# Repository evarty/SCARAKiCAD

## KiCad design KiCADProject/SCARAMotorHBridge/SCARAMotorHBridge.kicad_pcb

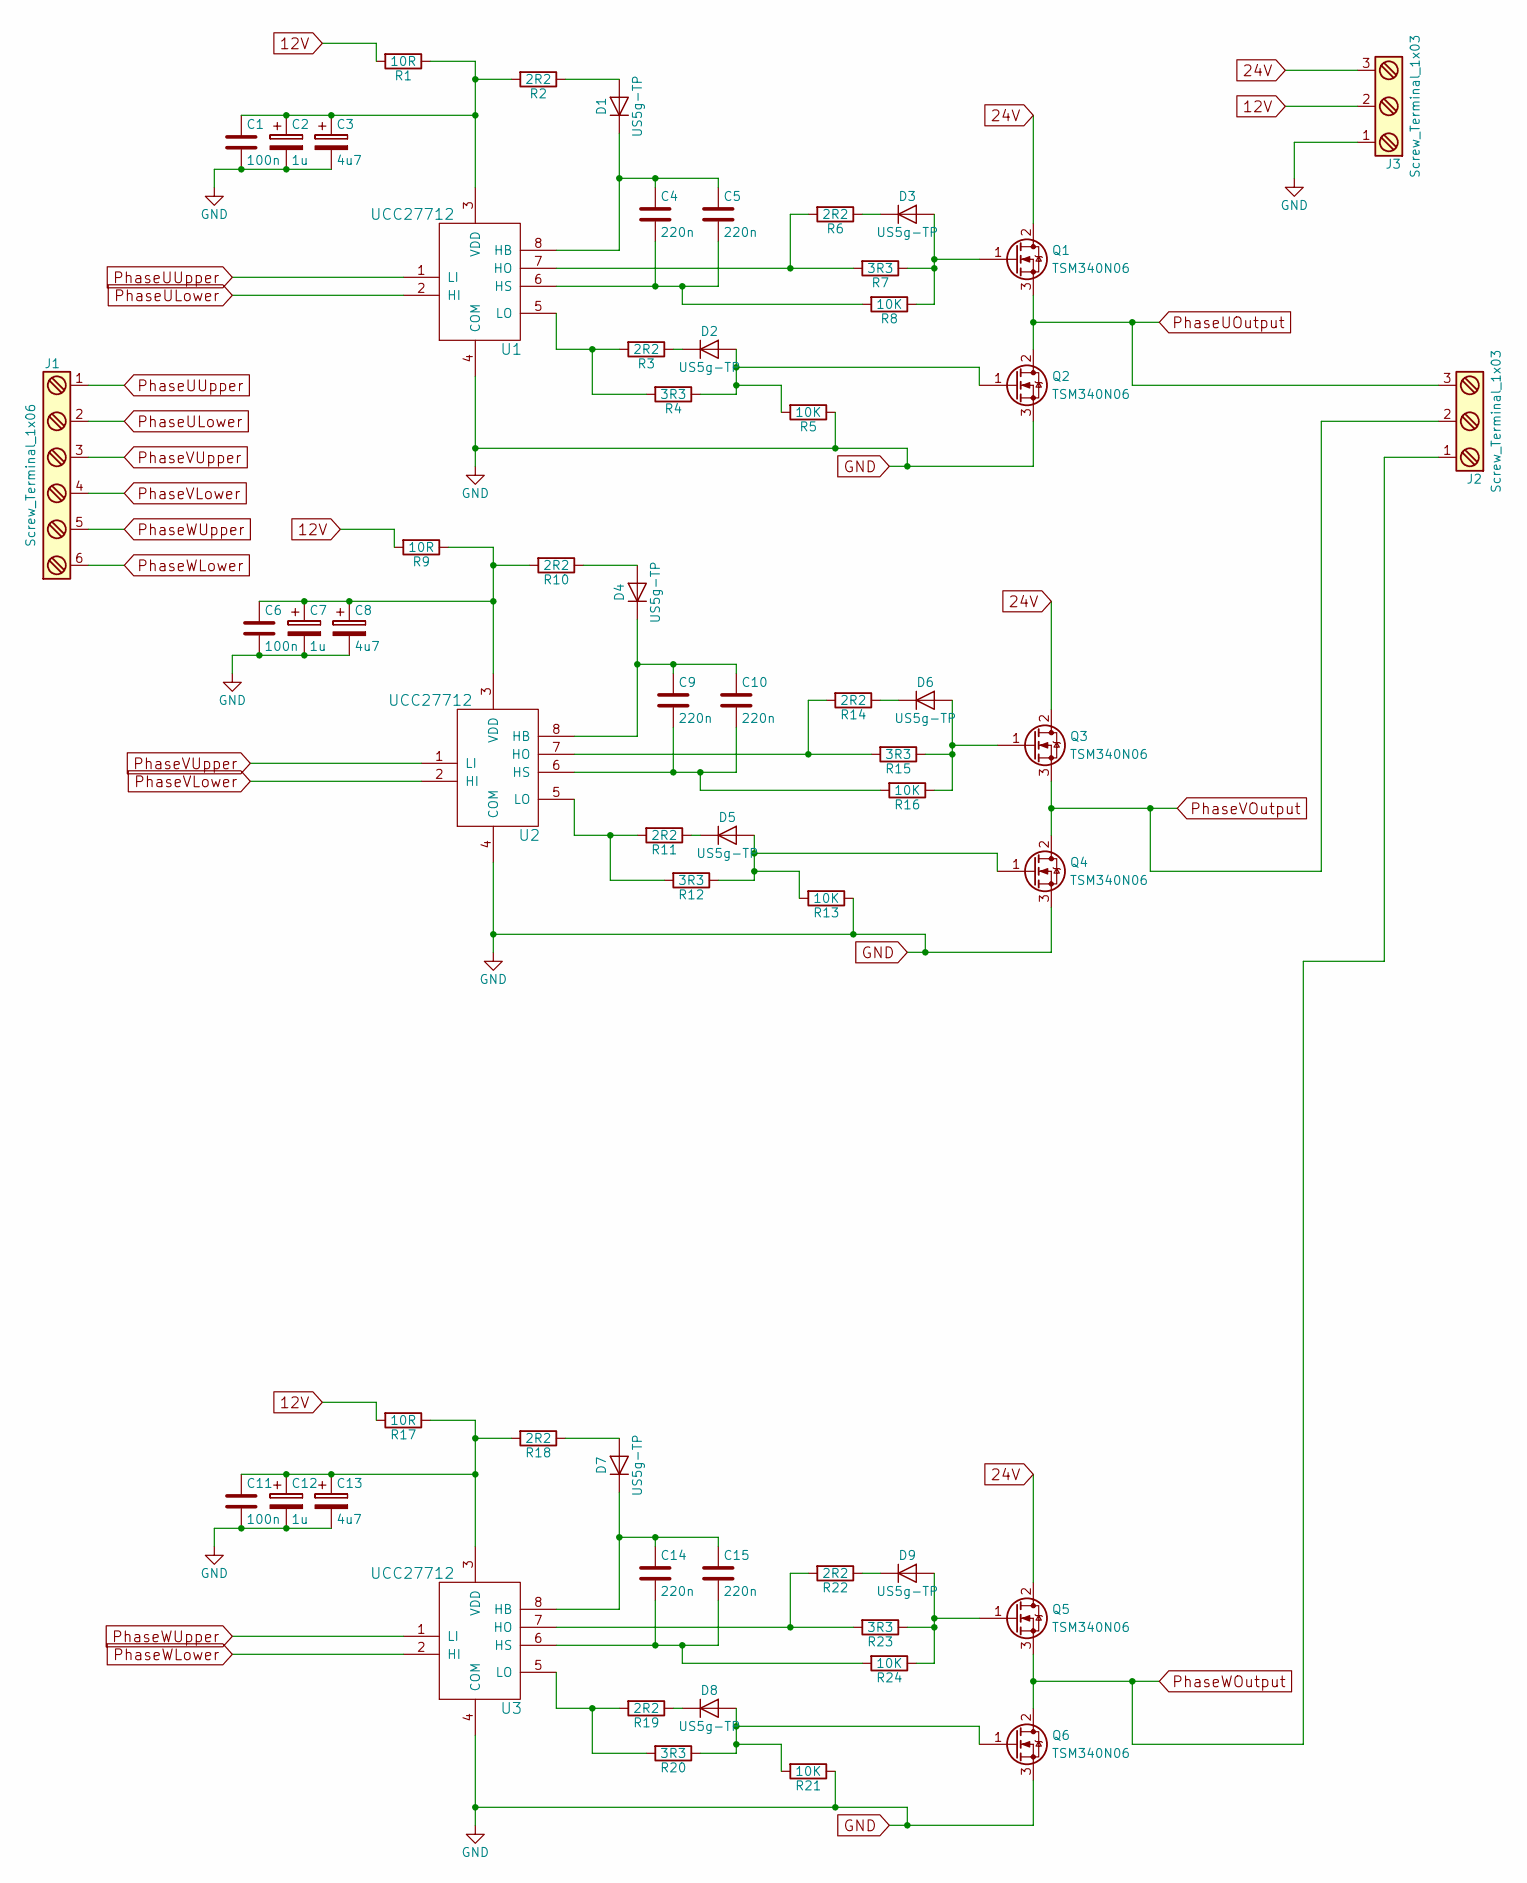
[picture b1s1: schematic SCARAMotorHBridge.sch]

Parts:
C1, C6, C11: 100n; C_0603_HandSoldering
C2, C7, C12: 1u; C_0805_HandSoldering
C3, C8, C13: 4u7; C_0805_HandSoldering
C4, C5, C9, C10, C14, C15: 220n; C_0805_HandSoldering
D1, D2, D3, D4, D5, D6, D7, D8, D9: US5g-TP; DO-214AB_Handsoldering
J1: Screw_Terminal_1x06; 6TermScrewTerminal
J2, J3: Screw_Terminal_1x03; 3TermScrewTerminal
Q1, Q2, Q3, Q4, Q5, Q6: TSM340N06; TO-252-2Lead
R1, R9, R17: 10R; R_1206_HandSoldering
R2, R3, R6, R10, R11, R14, R18, R19, R22: 2R2; R_1206_HandSoldering
R4, R7, R12, R15, R20, R23: 3R3; R_1206_HandSoldering
R5, R8, R13, R16, R21, R24: 10K; R_0805_HandSoldering
U1, U2, U3: UCC27712; SOIC-8-N

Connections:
12V: J3.2, R1.2, R9.2, R17.2
24V: J3.3, Q1.2 (D), Q3.2 (D), Q5.2 (D)
GND: C1.2, C2.2, C3.2, C6.2, C7.2, C8.2, C11.2, C12.2, C13.2, J3.1, Q2.3 (S), Q4.3 (S), Q6.3 (S), R5.1, R13.1, R21.1, U1.4 (COM), U2.4 (COM), U3.4 (COM)
unnamed: C1.1, C2.1, C3.1, R1.1, R2.2, U1.3 (VDD)
unnamed: C4.1, C5.1, D1.1 (K), U1.8 (HB)
unnamed: C4.2, C5.2, R8.2, U1.6 (HS)
unnamed: C6.1, C7.1, C8.1, R9.1, R10.2, U2.3 (VDD)
unnamed: C9.1, C10.1, D4.1 (K), U2.8 (HB)
unnamed: C9.2, C10.2, R16.2, U2.6 (HS)
unnamed: C11.1, C12.1, C13.1, R17.1, R18.2, U3.3 (VDD)
unnamed: C14.1, C15.1, D7.1 (K), U3.8 (HB)
unnamed: C14.2, C15.2, R24.2, U3.6 (HS)
unnamed: D1.2 (A), R2.1
unnamed: D2.1 (K), R3.1
unnamed: D2.2 (A), Q2.1 (G), R4.1, R5.2
unnamed: D3.1 (K), R6.1
unnamed: D3.2 (A), Q1.1 (G), R7.1, R8.1
unnamed: D4.2 (A), R10.1
unnamed: D5.1 (K), R11.1
unnamed: D5.2 (A), Q4.1 (G), R12.1, R13.2
unnamed: D6.1 (K), R14.1
unnamed: D6.2 (A), Q3.1 (G), R15.1, R16.1
unnamed: D7.2 (A), R18.1
unnamed: D8.1 (K), R19.1
unnamed: D8.2 (A), Q6.1 (G), R20.1, R21.2
unnamed: D9.1 (K), R22.1
unnamed: D9.2 (A), Q5.1 (G), R23.1, R24.1
unnamed: R3.2, R4.2, U1.5 (LO)
unnamed: R6.2, R7.2, U1.7 (HO)
unnamed: R11.2, R12.2, U2.5 (LO)
unnamed: R14.2, R15.2, U2.7 (HO)
unnamed: R19.2, R20.2, U3.5 (LO)
unnamed: R22.2, R23.2, U3.7 (HO)
PhaseULower: J1.2, U1.2 (HI)
PhaseUOutput: J2.3, Q1.3 (S), Q2.2 (D)
PhaseUUpper: J1.1, U1.1 (LI)
PhaseVLower: J1.4, U2.2 (HI)
PhaseVOutput: J2.2, Q3.3 (S), Q4.2 (D)
PhaseVUpper: J1.3, U2.1 (LI)
PhaseWLower: J1.6, U3.2 (HI)
PhaseWOutput: J2.1, Q5.3 (S), Q6.2 (D)
PhaseWUpper: J1.5, U3.1 (LI)

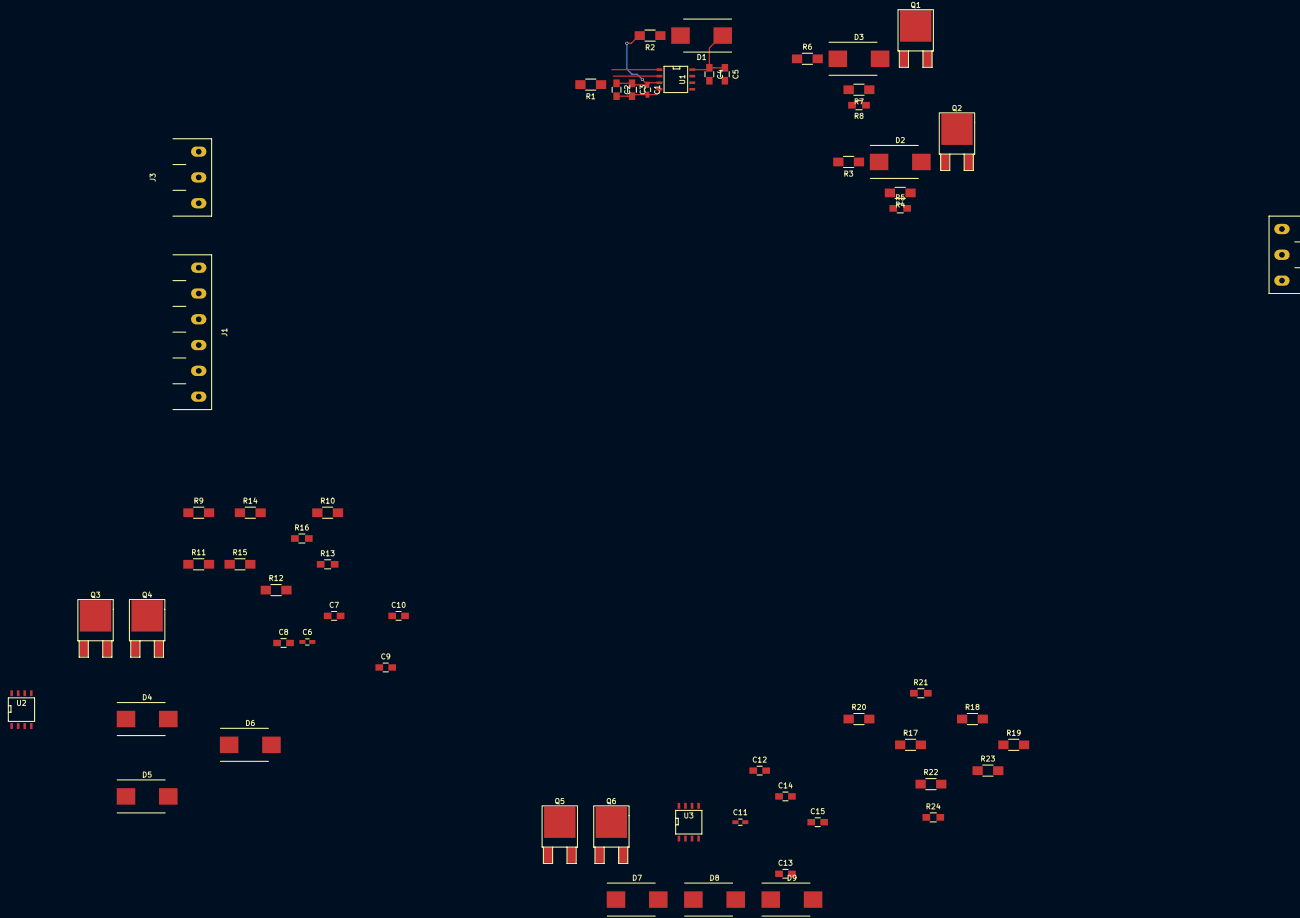
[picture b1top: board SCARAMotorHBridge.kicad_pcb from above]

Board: 2 copper layers, 60 parts (0 on the bottom side), 42 nets.

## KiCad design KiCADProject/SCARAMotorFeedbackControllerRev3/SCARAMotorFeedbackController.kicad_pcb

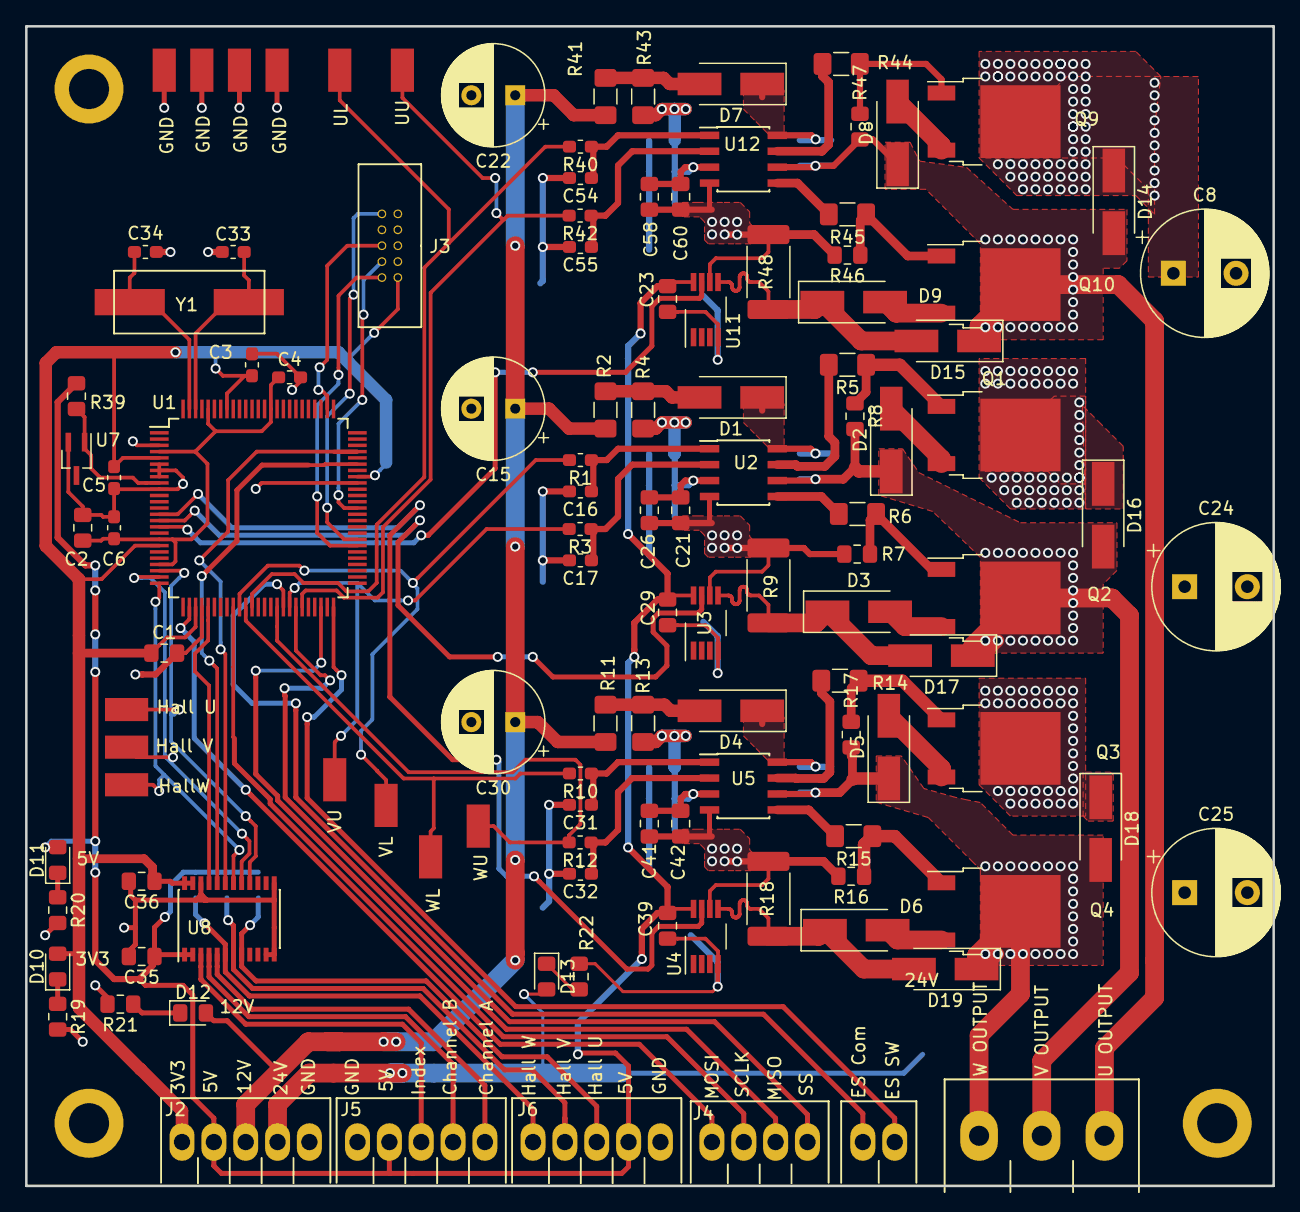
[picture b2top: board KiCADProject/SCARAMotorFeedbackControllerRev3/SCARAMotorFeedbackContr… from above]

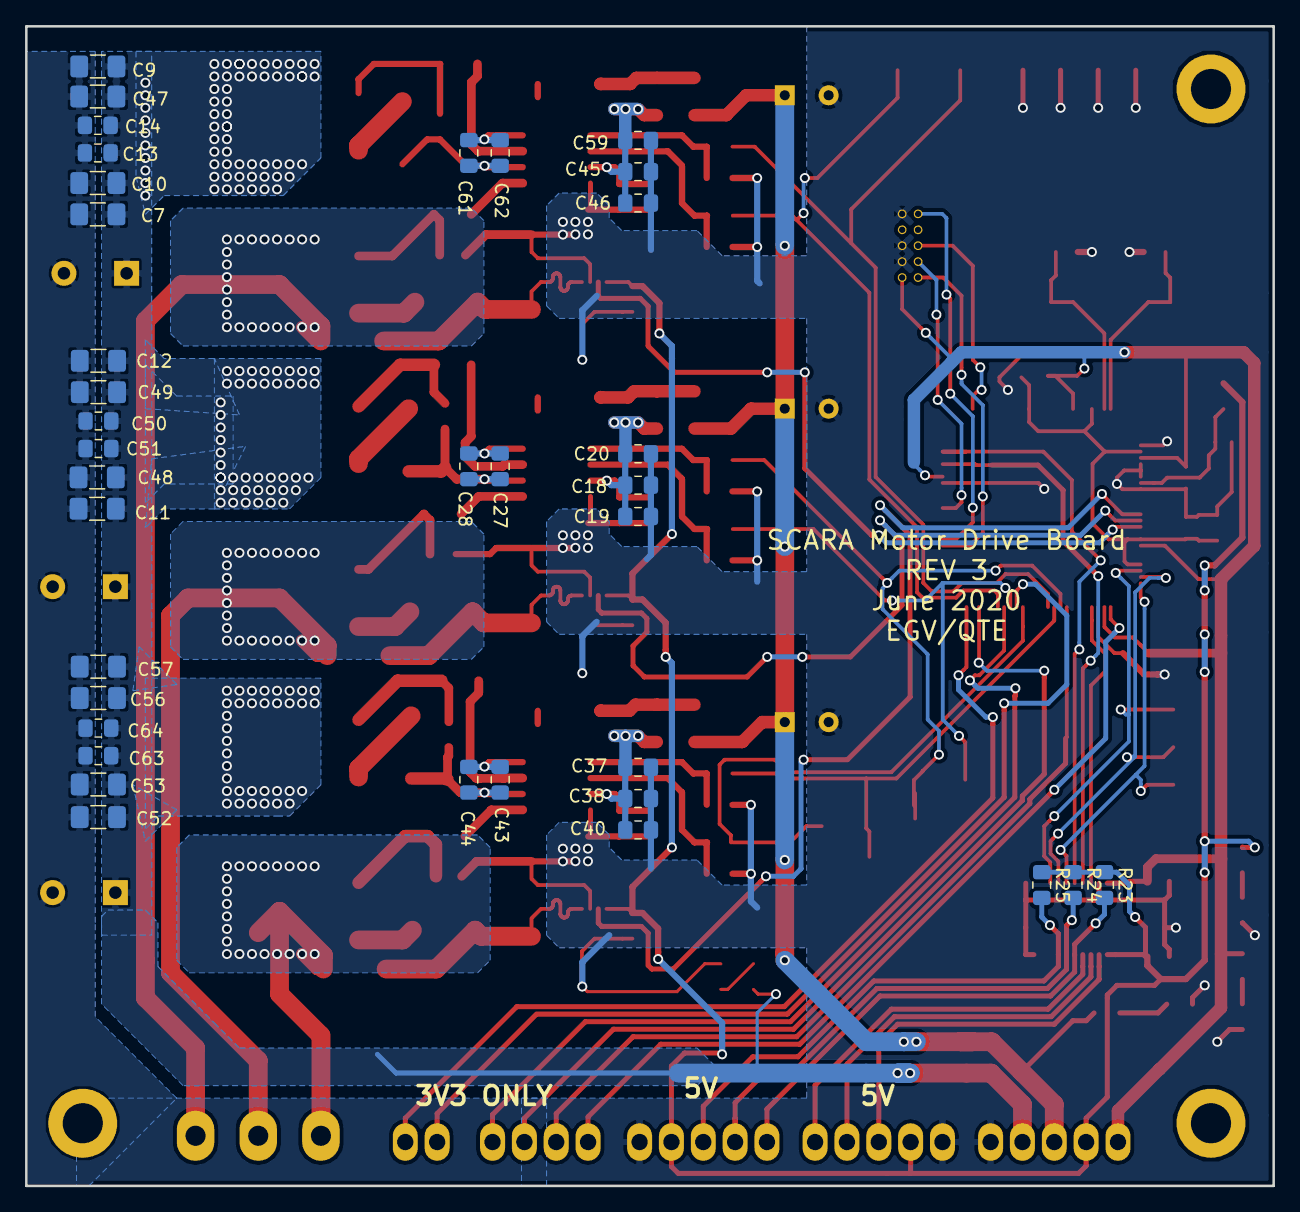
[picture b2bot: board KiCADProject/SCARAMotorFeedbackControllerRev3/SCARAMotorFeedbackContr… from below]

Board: 2 copper layers, 99.5 x 92.5 mm, 154 parts (36 on the bottom side), 83 nets.

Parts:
C1, C2: 1u; C_0805_2012Metric_Pad1.15x1.40mm_HandSolder
C3, C4: 0u1; C_0603_1608Metric_Pad1.05x0.95mm_HandSolder
C5, C6: 10n; C_0603_1608Metric_Pad1.05x0.95mm_HandSolder
C7, C9, C10, C11, C12, C47, C48, C49, C52, C53, C56, C57: 10u; C_1206_3216Metric_Pad1.42x1.75mm_HandSolder
C8, C24, C25: 470u; CP_Radial_D10.0mm_P5.00mm
C13, C14, C50, C51, C63, C64: u1; C_0805_2012Metric_Pad1.15x1.40mm_HandSolder
C15, C22, C30: 47u; CP_Radial_D8.0mm_P3.50mm
C16, C17, C31, C32, C54, C55: 120p; C_0603_1608Metric_Pad1.05x0.95mm_HandSolder
C18, C19, C37, C38, C45, C46: 10u; C_0805_2012Metric_Pad1.15x1.40mm_HandSolder
C20, C21, C26, C27, C28, C40, C41, C42, C43, C44, C58, C59, C60, C61, C62: u22; C_0805_2012Metric_Pad1.15x1.40mm_HandSolder
C23, C29, C35, C36, C39: 0u1; C_0805_2012Metric_Pad1.15x1.40mm_HandSolder
C33, C34: 13p; C_0603_1608Metric_Pad1.05x0.95mm_HandSolder
D1, D2, D3, D4, D5, D6, D7, D8, D9, D14, D15, D16, D17, D18, D19: D; D_SMA_Handsoldering
D10, D11, D12, D13: LED_ALT; LED_0805_2012Metric_Pad1.15x1.40mm_HandSolder
GND: TestPoint
GND#2, GND#3, GND#4: TestPoint
Hall U: TestPoint
Hall V: TestPoint
HallW: TestPoint
J1: Conn_01x02_Female; 2TermScrewTerminal
J2: Screw_Terminal_01x05; 5TermScrewTerminal
J3: SWD/JTAG Header; SWDHeader
J4: SPI Header; 4TermScrewTerminal
J5: EncoderInput; 5TermScrewTerminal
J6: HallInput; 5TermScrewTerminal
J9: Screw_Terminal_1x03; 3TermScrewTerminal
Q1, Q2, Q3, Q4, Q9, Q10: Q_NMOS_GDS; TO-252-2
R1, R3, R10, R12, R40, R42: 59R; R_0603_1608Metric_Pad1.05x0.95mm_HandSolder
R2, R4, R11, R13, R41, R43: 2R2; R_1206_3216Metric_Pad1.42x1.75mm_HandSolder
R5, R6, R14, R15, R44, R45: 3R3; R_1206_3216Metric_Pad1.42x1.75mm_HandSolder
R7, R8, R16, R17, R46, R47: 10K; R_0805_2012Metric_Pad1.15x1.40mm_HandSolder
R9, R18, R48: R05; R_2512_6332Metric_Pad1.52x3.35mm_HandSolder
R19, R39: 120R; R_0805_2012Metric_Pad1.15x1.40mm_HandSolder
R20: 240R; R_0805_2012Metric_Pad1.15x1.40mm_HandSolder
R21, R22: 1K; R_0805_2012Metric_Pad1.15x1.40mm_HandSolder
R23, R24, R25: 2k2; R_0805_2012Metric_Pad1.15x1.40mm_HandSolder
U1: ATSAM4E16CB-AN-ND; LQFP-100_14x14mm_P0.5mm
U2, U5, U12: UCC27712; SOIC-8_3.9x4.9mm_P1.27mm
U3, U4, U11: INA2180; VSSOP-8_3.0x3.0mm_P0.65mm
U7: LM4040; SOT-323_SC-70_Handsoldering
U8: 74LVC4245A; TSSOP-24_4.4x7.8mm_P0.65mm
UL: TestPoint
UU: TestPoint
VL: TestPoint
VU: TestPoint
WL: TestPoint
WU: TestPoint
Y1: 12MHzCrystal; SMDCrystalABLS12

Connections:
3V3: C1.1, C3.1, C5.1, C36.1, D10.2, J2.5, J3.1, U1.5, U1.19, U1.28, U1.68, U1.93, U8.23, U8.24
3V3Ref: R39.2, U1.9, U7.1
5V: C23.1, C29.1, C35.1, C39.1, D11.2, J2.4, J5.4, J6.2, R23.1, R24.1, R25.1, R39.1, U3.8, U4.8, U8.1, U8.2, U11.8
12V: C15.1, C22.1, C30.1, D12.2, J2.3, R2.2, R11.2, R41.2
24V: C7.1, C8.1, C9.1, C10.1, C11.1, C12.1, C13.1, C14.1, C24.1, C25.1, C47.1, C48.1, C49.1, C50.1, C51.1, C52.1, C53.1, C56.1, C57.1, C63.1, C64.1, D13.2, D14.1, D16.1, D18.1, J2.2, Q1.2, Q3.2, Q9.2
ChannelA: J5.1, U8.5
ChannelAShift: U1.72, U8.19
ChannelB: J5.2, U8.4
ChannelBShift: U1.70, U8.20
CurrentSenseU: U1.16, U11.7
CurrentSenseV: U1.15, U3.7
CurrentSenseW: U1.14, U4.7
EndstopCommon: J1.2, U1.42
EndstopSwitch: J1.1, U1.50
GND: C1.2, C2.2, C3.2, C4.2, C5.2, C6.2, C7.2, C8.2, C9.2, C10.2, C11.2, C12.2, C13.2, C14.2, C15.2, C16.2, C17.2, C18.2, C19.2, C20.2, C21.2, C22.2, C23.2, C24.2, C25.2, C26.2, C29.2, C30.2, C31.2, C32.2, C33.1, C34.1, C35.2, C36.2, C37.2, C38.2, C39.2, C40.2, C41.2, C42.2, C45.2, C46.2, C47.2, C48.2, C49.2, C50.2, C51.2, C52.2, C53.2, C54.2, C55.2, C56.2, C57.2, C58.2, C59.2, C60.2, C63.2, C64.2, GND.1, GND#2.1, GND#3.1, GND#4.1, J2.1, J3.3, J3.5, J3.9, J5.5, J6.1, R7.2, R9.2, R16.2, R18.2, R19.2, R20.2, R21.2, R22.2, R46.2, R48.2, U1.3, U1.6, U1.7, U1.8, U1.10, U1.29, U1.67, U2.4, U3.4, U3.6, U4.4, U4.6, U5.4, U7.2, U8.11, U8.12, U8.13, U8.22, U11.4, U11.6, U12.4
HallU: J6.3, R25.2, U8.8
HallUShift: Hall U.1, U1.23, U8.16
HallV: J6.4, R24.2, U8.7
HallVShift: Hall V.1, U1.24, U8.17
HallW: J6.5, R23.2, U8.6
HallWShift: HallW.1, U1.25, U8.18
IN+2U: D9.1, D15.2, R48.1, U11.5
IN+2V: D3.1, D17.2, R9.1, U3.5
IN+2W: D6.1, D19.2, R18.1, U4.5
Index: J5.3, U8.3
IndexShift: U1.30, U8.21
MISO: J4.2, U1.48
MOSI: J4.4, U1.27
unnamed: C2.1, C4.1, C6.1, U1.4, U1.18, U1.22, U1.86, U1.96
unnamed: C16.1, R1.1, U2.1
unnamed: C17.1, R3.1, U2.2
unnamed: C18.1, C19.1, C20.1, C21.1, C26.1, R4.1, U2.3
unnamed: C27.2, C28.2, D1.1, U2.8
unnamed: C31.1, R10.1, U5.1
unnamed: C32.1, R12.1, U5.2
unnamed: C33.2, U1.98, Y1.1
unnamed: C34.2, U1.99, Y1.2
unnamed: C37.1, C38.1, C40.1, C41.1, C42.1, R13.1, U5.3
unnamed: C43.2, C44.2, D4.1, U5.8
unnamed: C45.1, C46.1, C58.1, C59.1, C60.1, R43.1, U12.3
unnamed: C54.1, R40.1, U12.1
unnamed: C55.1, R42.1, U12.2
unnamed: C61.2, C62.2, D7.1, U12.8
unnamed: D1.2, R2.1, R4.2
unnamed: D2.2, Q1.3
unnamed: D3.2, Q2.3
unnamed: D4.2, R11.1, R13.2
unnamed: D5.2, Q3.3
unnamed: D6.2, Q4.3
unnamed: D7.2, R41.1, R43.2
unnamed: D8.2, Q9.3
unnamed: D9.2, Q10.3
unnamed: D10.1, R19.1
unnamed: D11.1, R20.1
unnamed: D12.1, R21.1
unnamed: D13.1, R22.1
unnamed: Q1.1, R5.1, R8.1
unnamed: Q2.1, R6.1, R7.1
unnamed: Q3.1, R14.1, R17.1
unnamed: Q4.1, R15.1, R16.1
unnamed: Q9.1, R44.1, R47.1
unnamed: Q10.1, R45.1, R46.1
unnamed: R5.2, U2.7
unnamed: R6.2, U2.5
unnamed: R14.2, U5.7
unnamed: R15.2, U5.5
unnamed: R44.2, U12.7
unnamed: R45.2, U12.5
PhaseULower: R40.2, U1.37, UL.1
PhaseUOutput: C61.1, C62.1, D8.1, D14.2, D15.1, J9.3, Q10.2, R47.2, U12.6
PhaseUUpper: R42.2, U1.45, UU.1
PhaseVLower: R1.2, U1.35, VL.1
PhaseVOutput: C27.1, C28.1, D2.1, D16.2, D17.1, J9.2, Q2.2, R8.2, U2.6
PhaseVUpper: R3.2, U1.43, VU.1
PhaseWLower: R10.2, U1.36, WL.1
PhaseWOutput: C43.1, C44.1, D5.1, D18.2, D19.1, J9.1, Q4.2, R17.2, U5.6
PhaseWUpper: R12.2, U1.41, WU.1
SCLK: J4.3, U1.34
SS: J4.1, U1.44
SWDCLK: J3.4, U1.63
SWDIO: J3.2, U1.57
SWO: J3.6, U1.77
nRESET: J3.10, U1.58

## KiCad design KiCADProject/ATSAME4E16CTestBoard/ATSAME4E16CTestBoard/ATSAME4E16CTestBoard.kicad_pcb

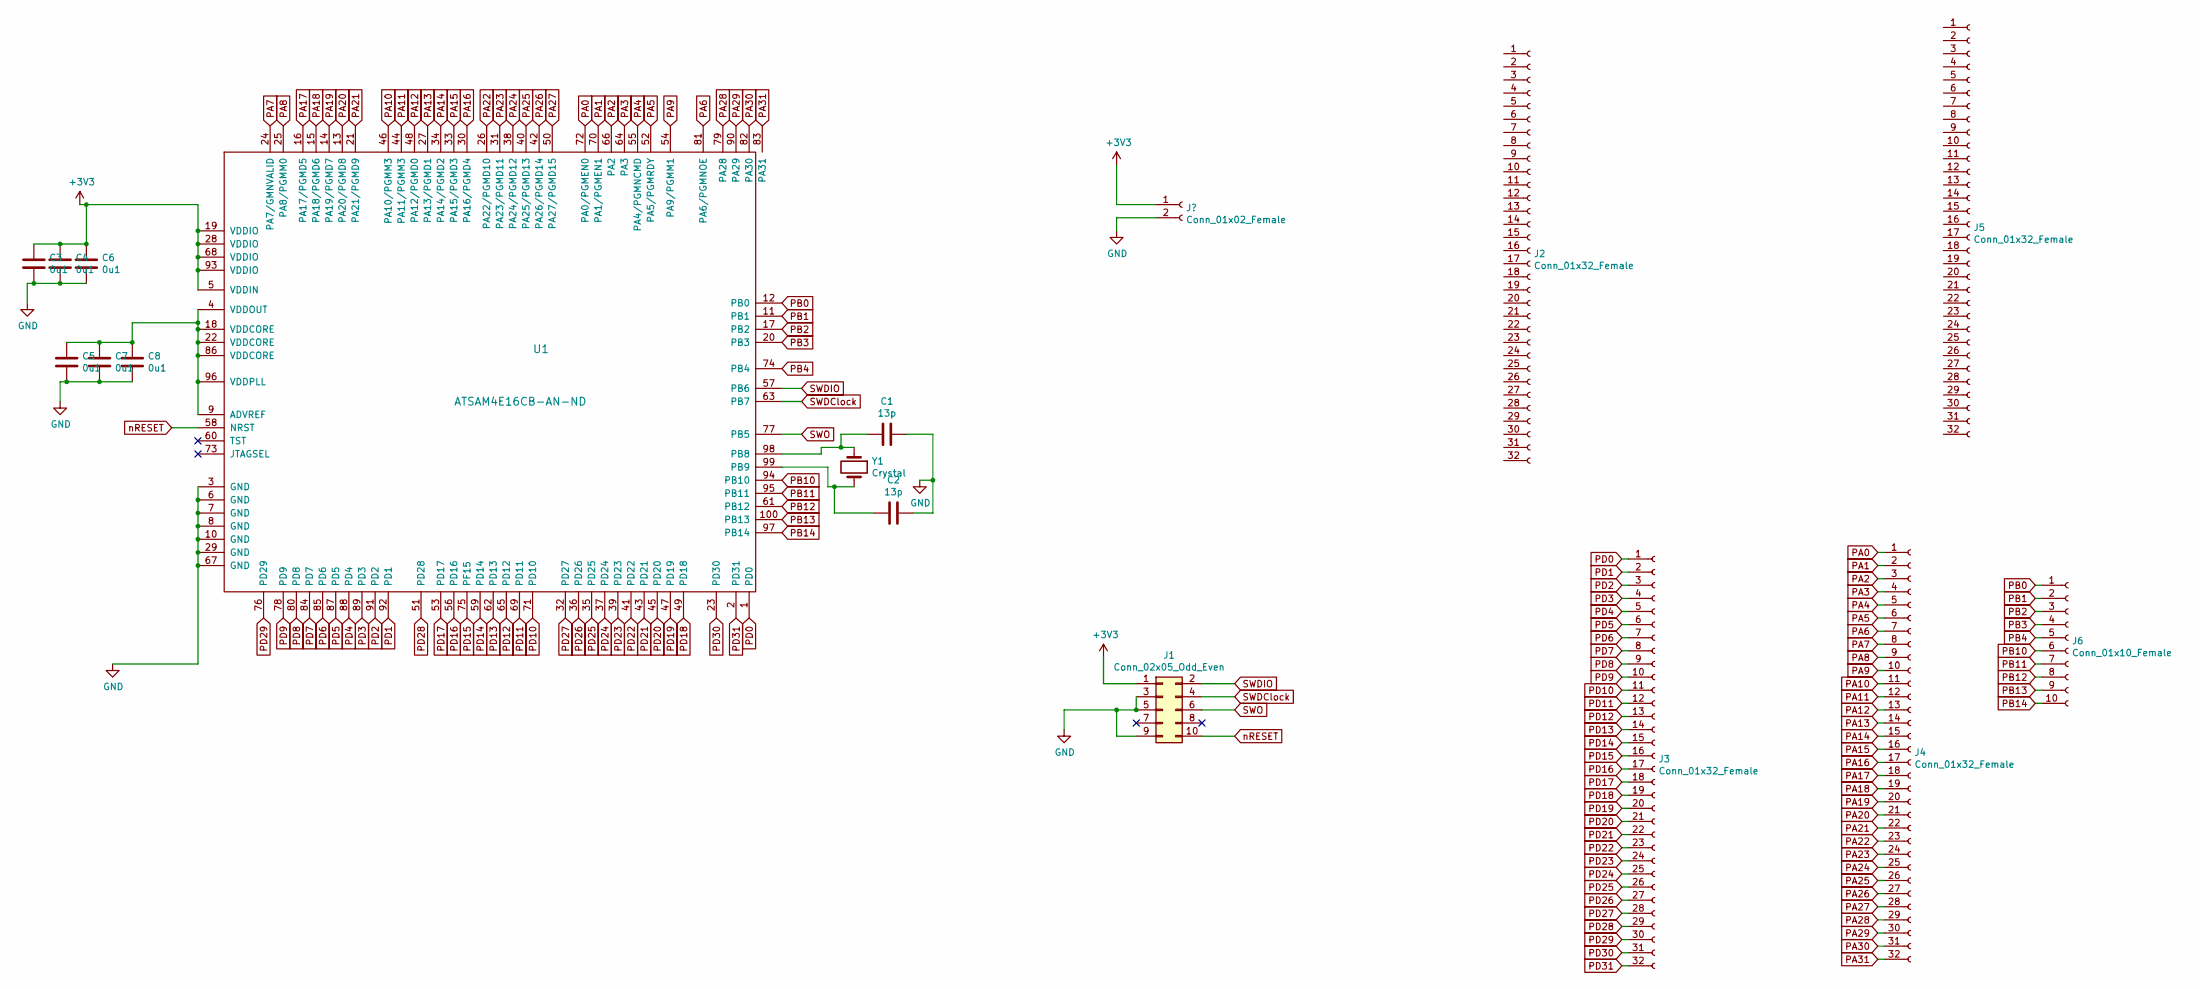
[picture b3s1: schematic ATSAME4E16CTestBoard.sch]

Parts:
C1, C2: 13p; C_0603_1608Metric_Pad1.05x0.95mm_HandSolder
C3, C4, C5, C6, C7, C8: 0u1; C_0603_1608Metric_Pad1.05x0.95mm_HandSolder
J1: Conn_02x05_Odd_Even; SWDHeader
J2, J3, J4, J5: Conn_01x32_Female; PinHeader_1x32_P2.54mm_Vertical
J6: Conn_01x10_Female; PinHeader_1x10_P2.54mm_Vertical
U1: ATSAM4E16CB-AN-ND; TQFP-100_12x12mm_P0.4mm
Y1: Crystal; SMDCrystalABLS12

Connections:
+3V3: C3.1, C4.1, C6.1, J1.1, U1.5 (VDDIN), U1.19 (VDDIO), U1.28 (VDDIO), U1.68 (VDDIO), U1.93 (VDDIO)
GND: C1.1, C2.1, C3.2, C4.2, C5.2, C6.2, C7.2, C8.2, J1.3, J1.5, J1.9, U1.3 (GND), U1.6 (GND), U1.7 (GND), U1.8 (GND), U1.10 (GND), U1.29 (GND), U1.67 (GND)
unnamed: C1.2, U1.98 (PB8), Y1.1
unnamed: C2.2, U1.99 (PB9), Y1.2
unnamed: C5.1, C7.1, C8.1, U1.4 (VDDOUT), U1.9 (ADVREF), U1.18 (VDDCORE), U1.22 (VDDCORE), U1.86 (VDDCORE), U1.96 (VDDPLL)
PA0: J4.1, U1.72 (PA0/PGMEN0)
PA1: J4.2, U1.70 (PA1/PGMEN1)
PA2: J4.3, U1.66 (PA2)
PA3: J4.4, U1.64 (PA3)
PA4: J4.5, U1.55 (PA4/PGMNCMD)
PA5: J4.6, U1.52 (PA5/PGMRDY)
PA6: J4.7, U1.81 (PA6/PGMNOE)
PA7: J4.8, U1.24 (PA7/GMNVALID)
PA8: J4.9, U1.25 (PA8/PGMM0)
PA9: J4.10, U1.54 (PA9/PGMM1)
PA10: J4.11, U1.46 (PA10/PGMM3)
PA11: J4.12, U1.44 (PA11/PGMM3)
PA12: J4.13, U1.48 (PA12/PGMD0)
PA13: J4.14, U1.27 (PA13/PGMD1)
PA14: J4.15, U1.34 (PA14/PGMD2)
PA15: J4.16, U1.33 (PA15/PGMD3)
PA16: J4.17, U1.30 (PA16/PGMD4)
PA17: J4.18, U1.16 (PA17/PGMD5)
PA18: J4.19, U1.15 (PA18/PGMD6)
PA19: J4.20, U1.14 (PA19/PGMD7)
PA20: J4.21, U1.13 (PA20/PGMD8)
PA21: J4.22, U1.21 (PA21/PGMD9)
PA22: J4.23, U1.26 (PA22/PGMD10)
PA23: J4.24, U1.31 (PA23/PGMD11)
PA24: J4.25, U1.38 (PA24/PGMD12)
PA25: J4.26, U1.40 (PA25/PGMD13)
PA26: J4.27, U1.42 (PA26/PGMD14)
PA27: J4.28, U1.50 (PA27/PGMD15)
PA28: J4.29, U1.79 (PA28)
PA29: J4.30, U1.90 (PA29)
PA30: J4.31, U1.82 (PA30)
PA31: J4.32, U1.83 (PA31)
PB0: J6.1, U1.12 (PB0)
PB1: J6.2, U1.11 (PB1)
PB2: J6.3, U1.17 (PB2)
PB3: J6.4, U1.20 (PB3)
PB4: J6.5, U1.74 (PB4)
PB10: J6.6, U1.94 (PB10)
PB11: J6.7, U1.95 (PB11)
PB12: J6.8, U1.61 (PB12)
PB13: J6.9, U1.100 (PB13)
PB14: J6.10, U1.97 (PB14)
PD0: J3.1, U1.1 (PD0)
PD1: J3.2, U1.92 (PD1)
PD2: J3.3, U1.91 (PD2)
PD3: J3.4, U1.89 (PD3)
PD4: J3.5, U1.88 (PD4)
PD5: J3.6, U1.87 (PD5)
PD6: J3.7, U1.85 (PD6)
PD7: J3.8, U1.84 (PD7)
PD8: J3.9, U1.80 (PD8)
PD9: J3.10, U1.78 (PD9)
PD10: J3.11, U1.71 (PD10)
PD11: J3.12, U1.69 (PD11)
PD12: J3.13, U1.65 (PD12)
PD13: J3.14, U1.62 (PD13)
PD14: J3.15, U1.59 (PD14)
PD15: J3.16, U1.75 (PF15)
PD16: J3.17, U1.56 (PD16)
PD17: J3.18, U1.53 (PD17)
PD18: J3.19, U1.49 (PD18)
PD19: J3.20, U1.47 (PD19)
PD20: J3.21, U1.45 (PD20)
PD21: J3.22, U1.43 (PD21)
PD22: J3.23, U1.41 (PD22)
PD23: J3.24, U1.39 (PD23)
PD24: J3.25, U1.37 (PD24)
PD25: J3.26, U1.35 (PD25)
PD26: J3.27, U1.36 (PD26)
PD27: J3.28, U1.32 (PD27)
PD28: J3.29, U1.51 (PD28)
PD29: J3.30, U1.76 (PD29)
PD30: J3.31, U1.23 (PD30)
PD31: J3.32, U1.2 (PD31)
SWDClock: J1.4, U1.63 (PB7)
SWDIO: J1.2, U1.57 (PB6)
SWO: J1.6, U1.77 (PB5)
nRESET: J1.10, U1.58 (NRST)

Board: 2 copper layers, 16 parts (0 on the bottom side), 83 nets, no tracks yet.

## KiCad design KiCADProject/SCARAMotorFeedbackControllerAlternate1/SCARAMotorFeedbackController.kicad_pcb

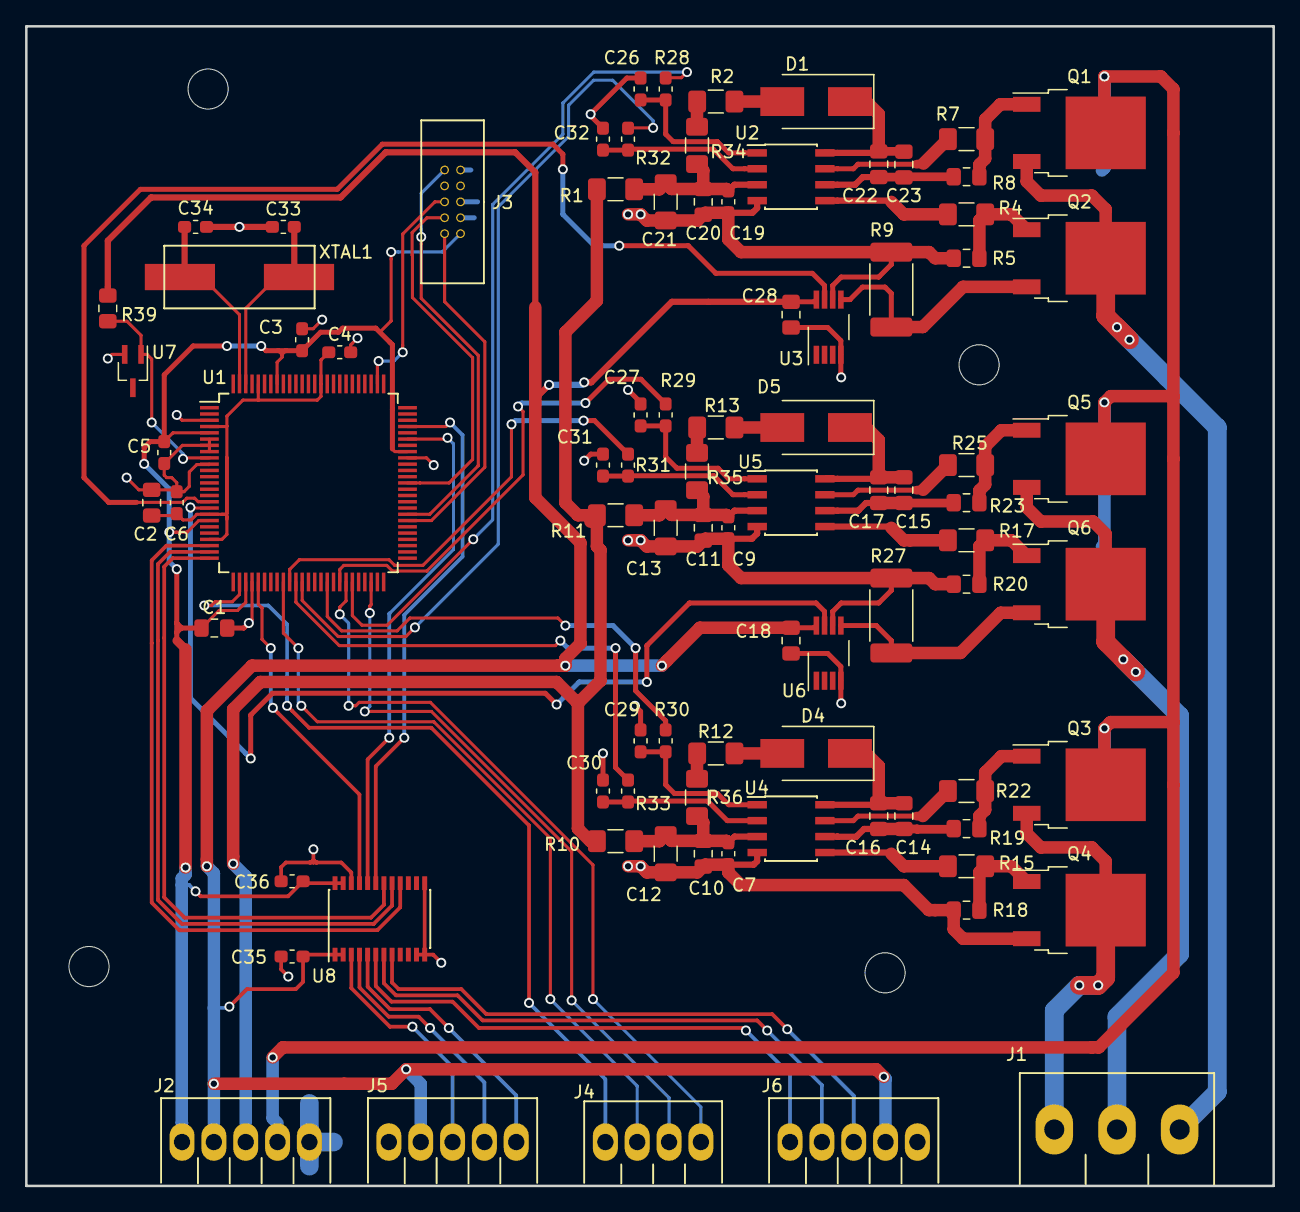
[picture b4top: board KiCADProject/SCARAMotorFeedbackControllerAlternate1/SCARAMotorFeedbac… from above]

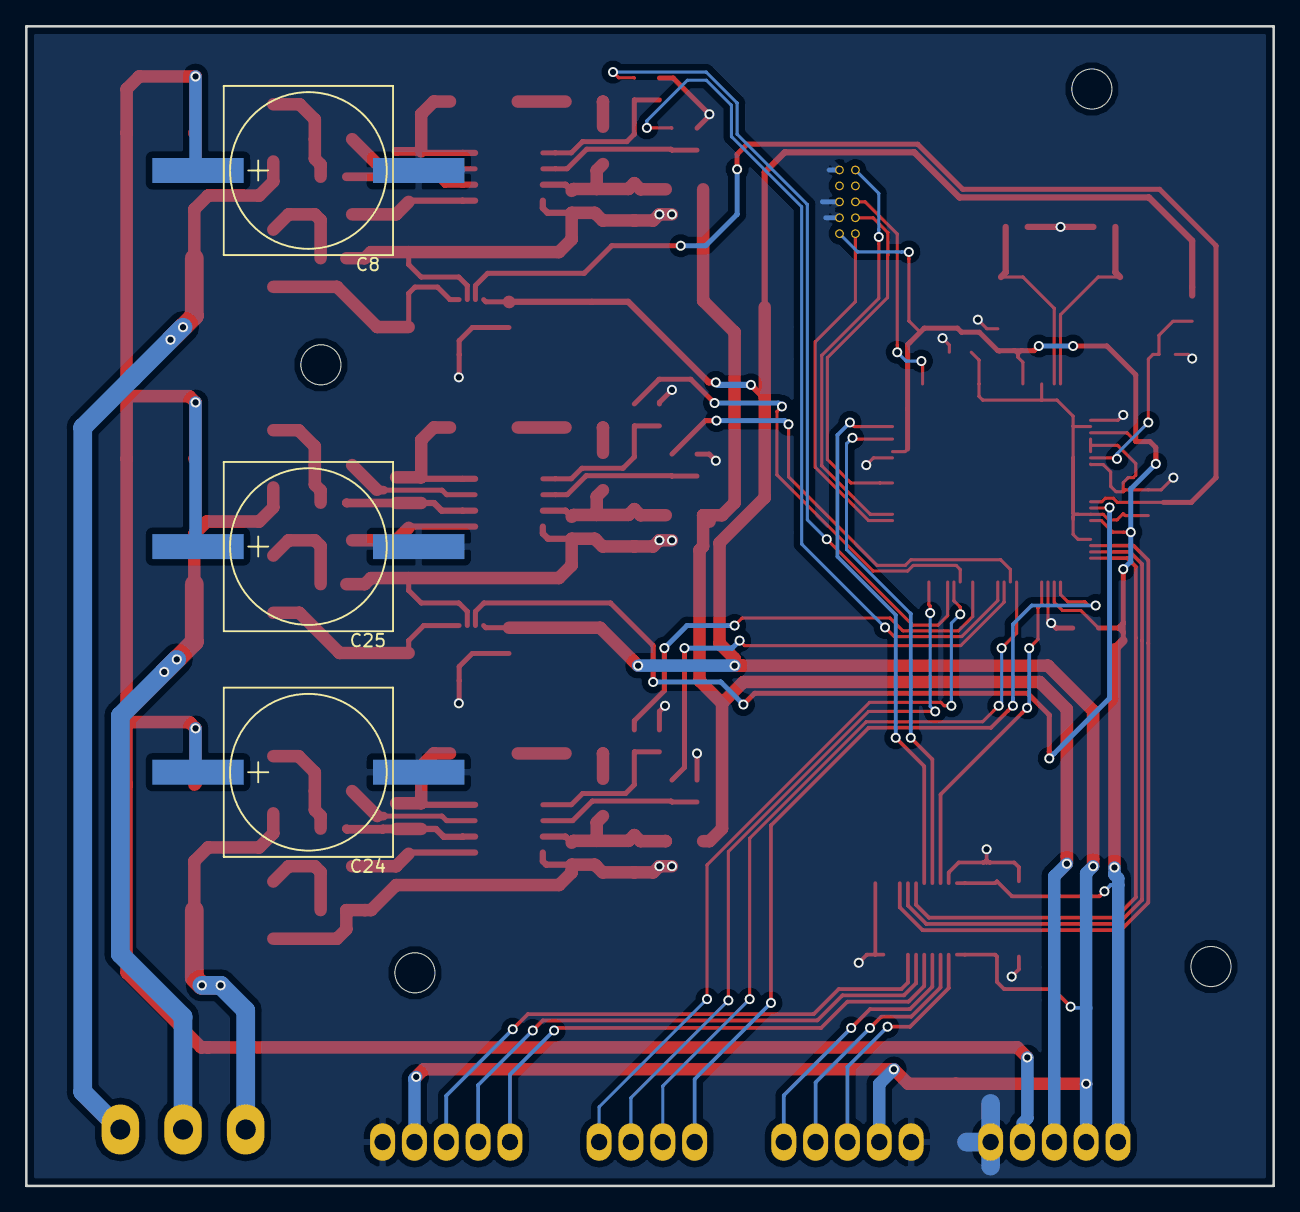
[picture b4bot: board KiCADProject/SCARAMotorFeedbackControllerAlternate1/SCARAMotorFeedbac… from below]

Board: 2 copper layers, 99.5 x 92.5 mm, 90 parts (3 on the bottom side), 75 nets.

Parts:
C1, C2, C10, C11, C20: 1u; C_0805_2012Metric_Pad1.15x1.40mm_HandSolder
C3, C4, C35, C36: 0u1; C_0603_1608Metric_Pad1.05x0.95mm_HandSolder
C5, C6: 10n; C_0603_1608Metric_Pad1.05x0.95mm_HandSolder
C7, C9, C19: 100n; C_0603_1608Metric_Pad1.05x0.95mm_HandSolder
C8, C24, C25: 470u; LargeSMDCap
C12, C13, C21: 4u7; C_1206_3216Metric_Pad1.42x1.75mm_HandSolder
C14, C15, C16, C17, C22, C23: 220n; C_0805_2012Metric_Pad1.15x1.40mm_HandSolder
C18, C28: 0u1; C_0805_2012Metric_Pad1.15x1.40mm_HandSolder
C26, C27, C29, C30, C31, C32: 120p; C_0603_1608Metric_Pad1.05x0.95mm_HandSolder
C33, C34: 13p; C_0603_1608Metric_Pad1.05x0.95mm_HandSolder
D1, D4, D5: US5g-TP; D_SMB_Handsoldering
J1: Screw_Terminal_1x03; 3TermScrewTerminal
J2: Screw_Terminal_01x05; 5TermScrewTerminal
J3: SWD/JTAG Header; SWDHeader
J4: SPI Header; 4TermScrewTerminal
J5: EncoderInput; 5TermScrewTerminal
J6: HallInput; 5TermScrewTerminal
Q1, Q2, Q3, Q4, Q5, Q6: TSM340N06; TO-252-2
R1, R10, R11: 10R; R_1206_3216Metric_Pad1.42x1.75mm_HandSolder
R2, R12, R13: 2R2; R_1206_3216Metric_Pad1.42x1.75mm_HandSolder
R4, R7, R15, R17, R22, R25: 3R3; R_1206_3216Metric_Pad1.42x1.75mm_HandSolder
R5, R8, R18, R19, R20, R23: 10K; R_0805_2012Metric_Pad1.15x1.40mm_HandSolder
R9, R27: R05; R_2512_6332Metric_Pad1.52x3.35mm_HandSolder
R28, R29, R30, R31, R32, R33: 59R; R_0603_1608Metric_Pad1.05x0.95mm_HandSolder
R34, R35, R36: 0R; R_1206_3216Metric_Pad1.42x1.75mm_HandSolder
R39: 120R; R_0805_2012Metric_Pad1.15x1.40mm_HandSolder
U1: ATSAM4E16CB-AN-ND; LQFP-100_14x14mm_P0.5mm
U2, U4, U5: UCC27712; SOIC-8_3.9x4.9mm_P1.27mm
U3, U6: INA2180; VSSOP-8_3.0x3.0mm_P0.65mm
U7: LM4040; SOT-323_SC-70_Handsoldering
U8: 74LVC4245A; TSSOP-24_4.4x7.8mm_P0.65mm
XTAL1: 12MHzCrystal; SMDCrystalABLS12

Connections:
3V3: C1.1, C3.1, C5.1, C36.1, J2.5, J3.1, U1.5, U1.19, U1.28, U1.68, U1.93, U8.23, U8.24
3V3Ref: R39.2, U1.9, U7.1
5V: C18.1, C28.1, C35.1, J2.4, J5.4, J6.2, R39.1, U3.8, U6.8, U8.1, U8.2
12V: J2.3, R1.2, R10.2, R11.2
24V: C8.1, C24.1, C25.1, J2.2, Q1.2, Q3.2, Q5.2
ChannelA: J5.1, U8.5
ChannelAShift: U1.72, U8.19
ChannelB: J5.2, U8.4
ChannelBShift: U1.70, U8.20
CurrentSenseU: U1.16, U3.7
CurrentSenseV: U1.17, U6.7
GND: C1.2, C2.2, C3.2, C4.2, C5.2, C6.2, C7.2, C8.2, C9.2, C10.2, C11.2, C12.2, C13.2, C18.2, C19.2, C20.2, C21.2, C24.2, C25.2, C26.2, C27.2, C28.2, C29.2, C30.2, C31.2, C32.2, C33.1, C34.1, C35.2, C36.2, J2.1, J3.3, J3.5, J3.9, J5.5, J6.1, Q4.3, R5.1, R9.2, R18.1, R20.1, R27.2, U1.3, U1.6, U1.7, U1.8, U1.10, U1.29, U1.67, U2.4, U3.4, U3.6, U4.4, U5.4, U6.4, U6.6, U7.2, U8.11, U8.12, U8.13, U8.22
HallU: J6.3, U8.8
HallUShift: U1.23, U8.16
HallV: J6.4, U8.7
HallVShift: U1.24, U8.17
HallW: J6.5, U8.6
HallWShift: U1.25, U8.18
IN+2U: Q2.3, R9.1, U3.5
IN+2V: Q6.3, R27.1, U6.5
Index: J5.3, U8.3
IndexShift: U1.30, U8.21
MISO: J4.2, U1.48
MOSI: J4.4, U1.27
unnamed: C2.1, C4.1, C6.1, U1.4, U1.18, U1.22, U1.86, U1.96
unnamed: C7.1, C10.1, C12.1, R10.1, R36.2, U4.3
unnamed: C9.1, C11.1, C13.1, R11.1, R35.2, U5.3
unnamed: C14.1, C16.1, D4.1, U4.8
unnamed: C14.2, C16.2, R19.2, U4.6
unnamed: C15.1, C17.1, D5.1, U5.8
unnamed: C15.2, C17.2, R23.2, U5.6
unnamed: C19.1, C20.1, C21.1, R1.1, R34.2, U2.3
unnamed: C22.1, C23.1, D1.1, U2.8
unnamed: C22.2, C23.2, R8.2, U2.6
unnamed: C26.1, R28.1, U2.1
unnamed: C27.1, R29.1, U5.1
unnamed: C29.1, R30.1, U4.1
unnamed: C30.1, R33.1, U4.2
unnamed: C31.1, R31.1, U5.2
unnamed: C32.1, R32.1, U2.2
unnamed: C33.2, U1.98, XTAL1.1
unnamed: C34.2, U1.99, XTAL1.2
unnamed: D1.2, R2.1
unnamed: D4.2, R12.1
unnamed: D5.2, R13.1
unnamed: Q1.1, R7.1, R8.1
unnamed: Q2.1, R4.1, R5.2
unnamed: Q3.1, R19.1, R22.1
unnamed: Q4.1, R15.1, R18.2
unnamed: Q5.1, R23.1, R25.1
unnamed: Q6.1, R17.1, R20.2
unnamed: R2.2, R34.1
unnamed: R4.2, U2.5
unnamed: R7.2, U2.7
unnamed: R12.2, R36.1
unnamed: R13.2, R35.1
unnamed: R15.2, U4.5
unnamed: R17.2, U5.5
unnamed: R22.2, U4.7
unnamed: R25.2, U5.7
PhaseULower: R32.2, U1.37
PhaseUOutput: J1.3, Q1.3, Q2.2
PhaseUUpper: R28.2, U1.45
PhaseVLower: R31.2, U1.35
PhaseVOutput: J1.2, Q5.3, Q6.2
PhaseVUpper: R29.2, U1.43
PhaseWLower: R33.2, U1.36
PhaseWOutput: J1.1, Q3.3, Q4.2
PhaseWUpper: R30.2, U1.41
SCLK: J4.3, U1.34
SS: J4.1, U1.44
SWDCLK: J3.4, U1.63
SWDIO: J3.2, U1.57
SWO: J3.6, U1.77
nRESET: J3.10, U1.58

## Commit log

2018-06-06 First commit to pi
